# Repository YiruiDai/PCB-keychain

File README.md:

# Flashing Keychain

This is a keychain with an LED that flashes with the push of a button!

## Schematic

## PCB

## BOM
2 Battery holder\
2 uF Capacitor\
2 NPN Transistor\
6 220 Resistor\
1 LED\
1 Push button

Made by @Yirui on Slack

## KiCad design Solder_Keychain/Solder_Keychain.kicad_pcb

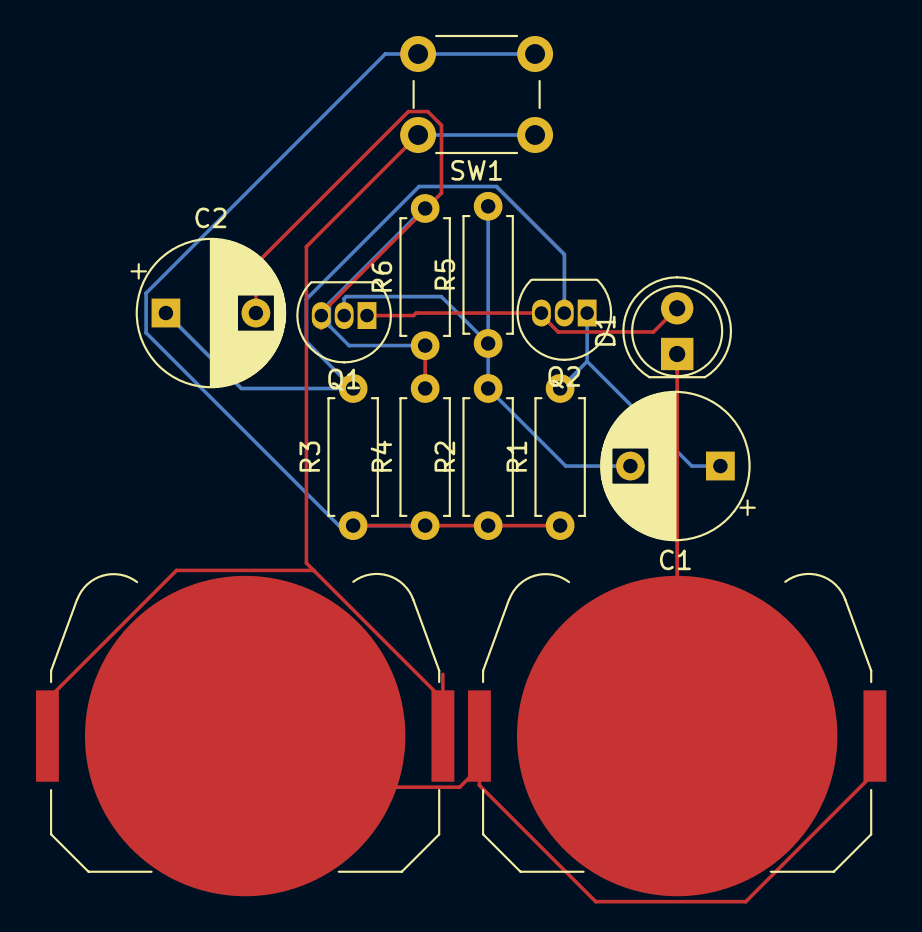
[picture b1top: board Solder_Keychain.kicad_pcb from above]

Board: 2 copper layers, 14 parts (0 on the bottom side), 9 nets.

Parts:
BT1, BT2: Battery_Cell; BatteryHolder_Keystone_3034_1x20mm
C1, C2: C; CP_Radial_D8.0mm_P5.00mm
D1: LED; LED_D5.0mm
Q1, Q2: 2N3904; TO-92_Inline
R1, R2, R3, R4, R5, R6: R; R_Axial_DIN0207_L6.3mm_D2.5mm_P7.62mm_Horizontal
SW1: SW_Push; SW_PUSH_6mm

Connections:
unnamed: BT1.1 (+), SW1.1
unnamed: BT1.2 (-), BT2.1 (+)
unnamed: BT2.2 (-), D1.1 (K)
unnamed: D1.2 (A), Q1.1 (E), Q2.3 (C)
unnamed: C1.2, Q1.2 (B), R2.2, R5.1, R5.2
unnamed: C2.2, Q1.3 (C), R4.2, R6.1, R6.2
unnamed: C2.1, Q2.2 (B), R3.2
unnamed: C1.1, Q2.1 (E), R1.2
unnamed: R1.1, R2.1, R3.1, R4.1, SW1.2
